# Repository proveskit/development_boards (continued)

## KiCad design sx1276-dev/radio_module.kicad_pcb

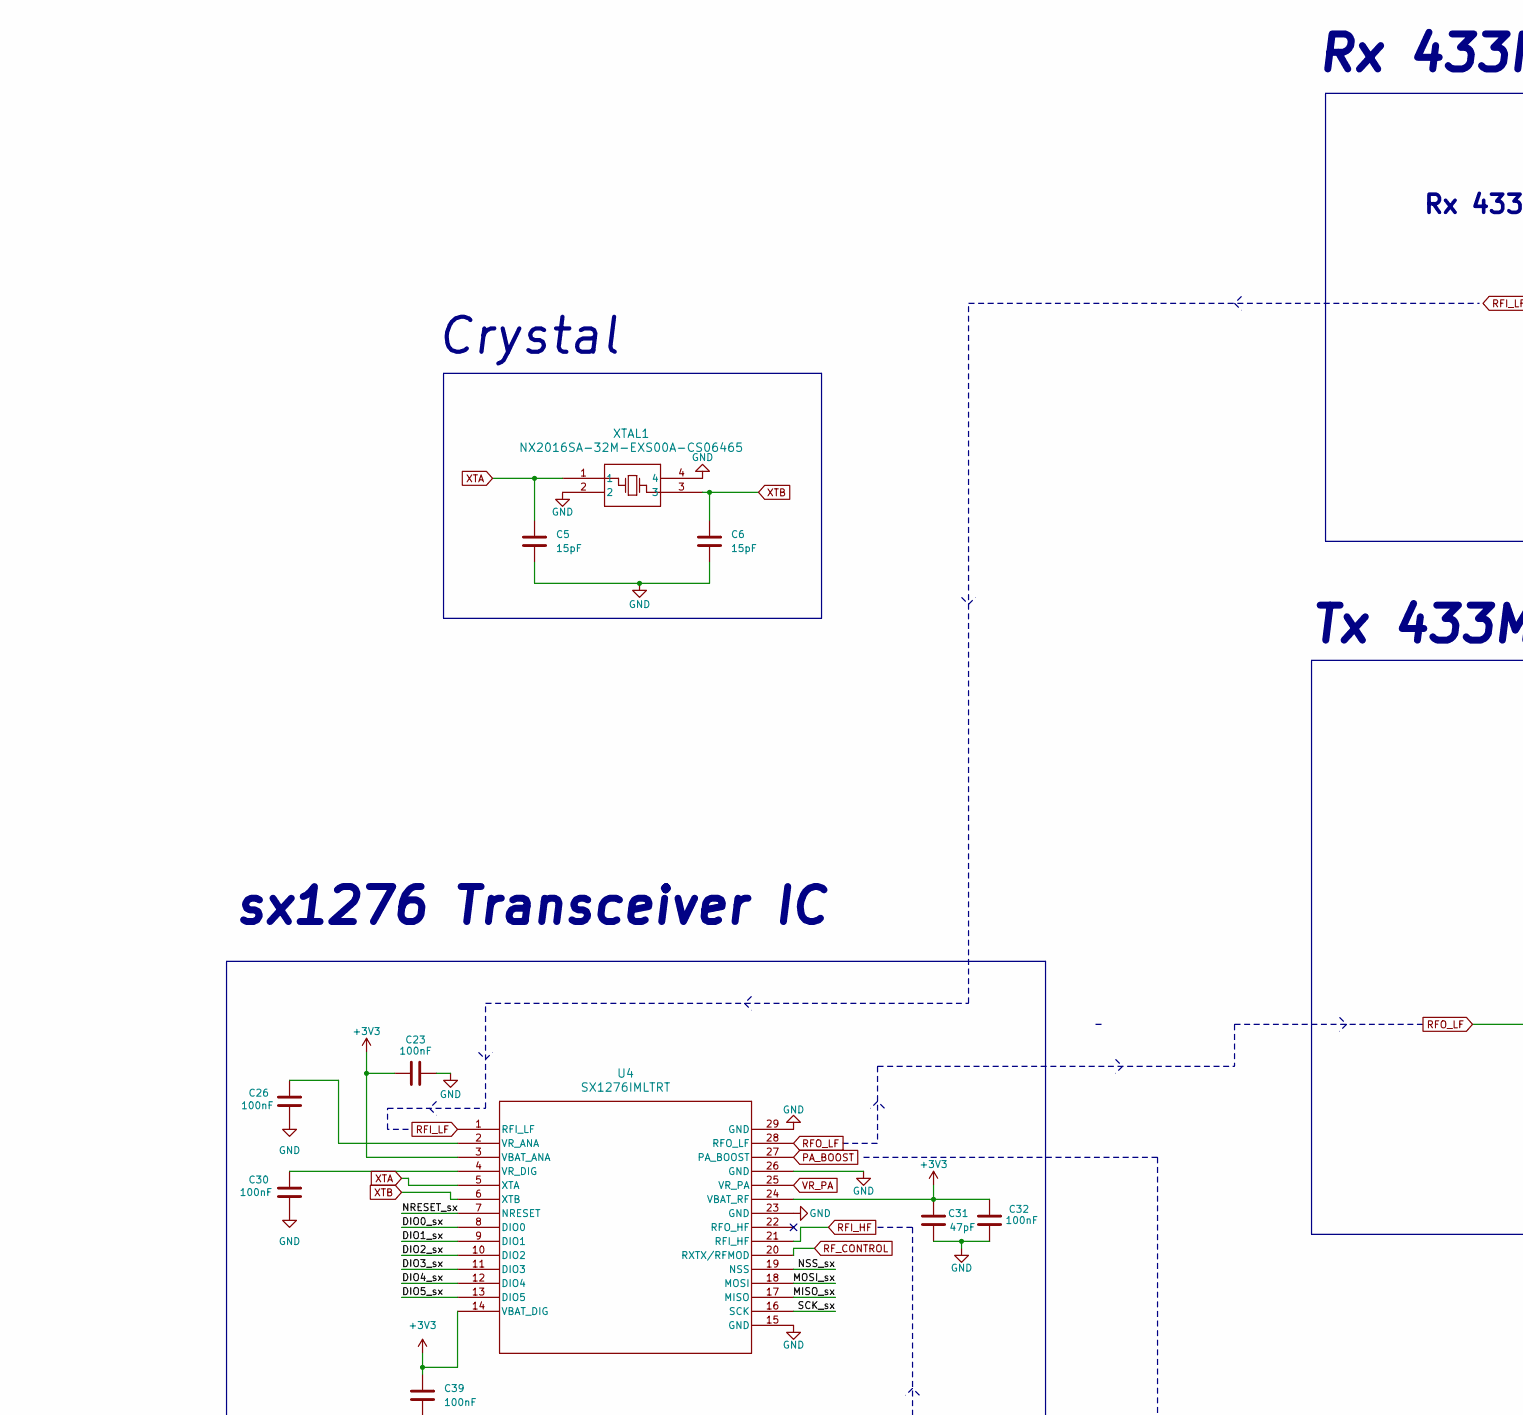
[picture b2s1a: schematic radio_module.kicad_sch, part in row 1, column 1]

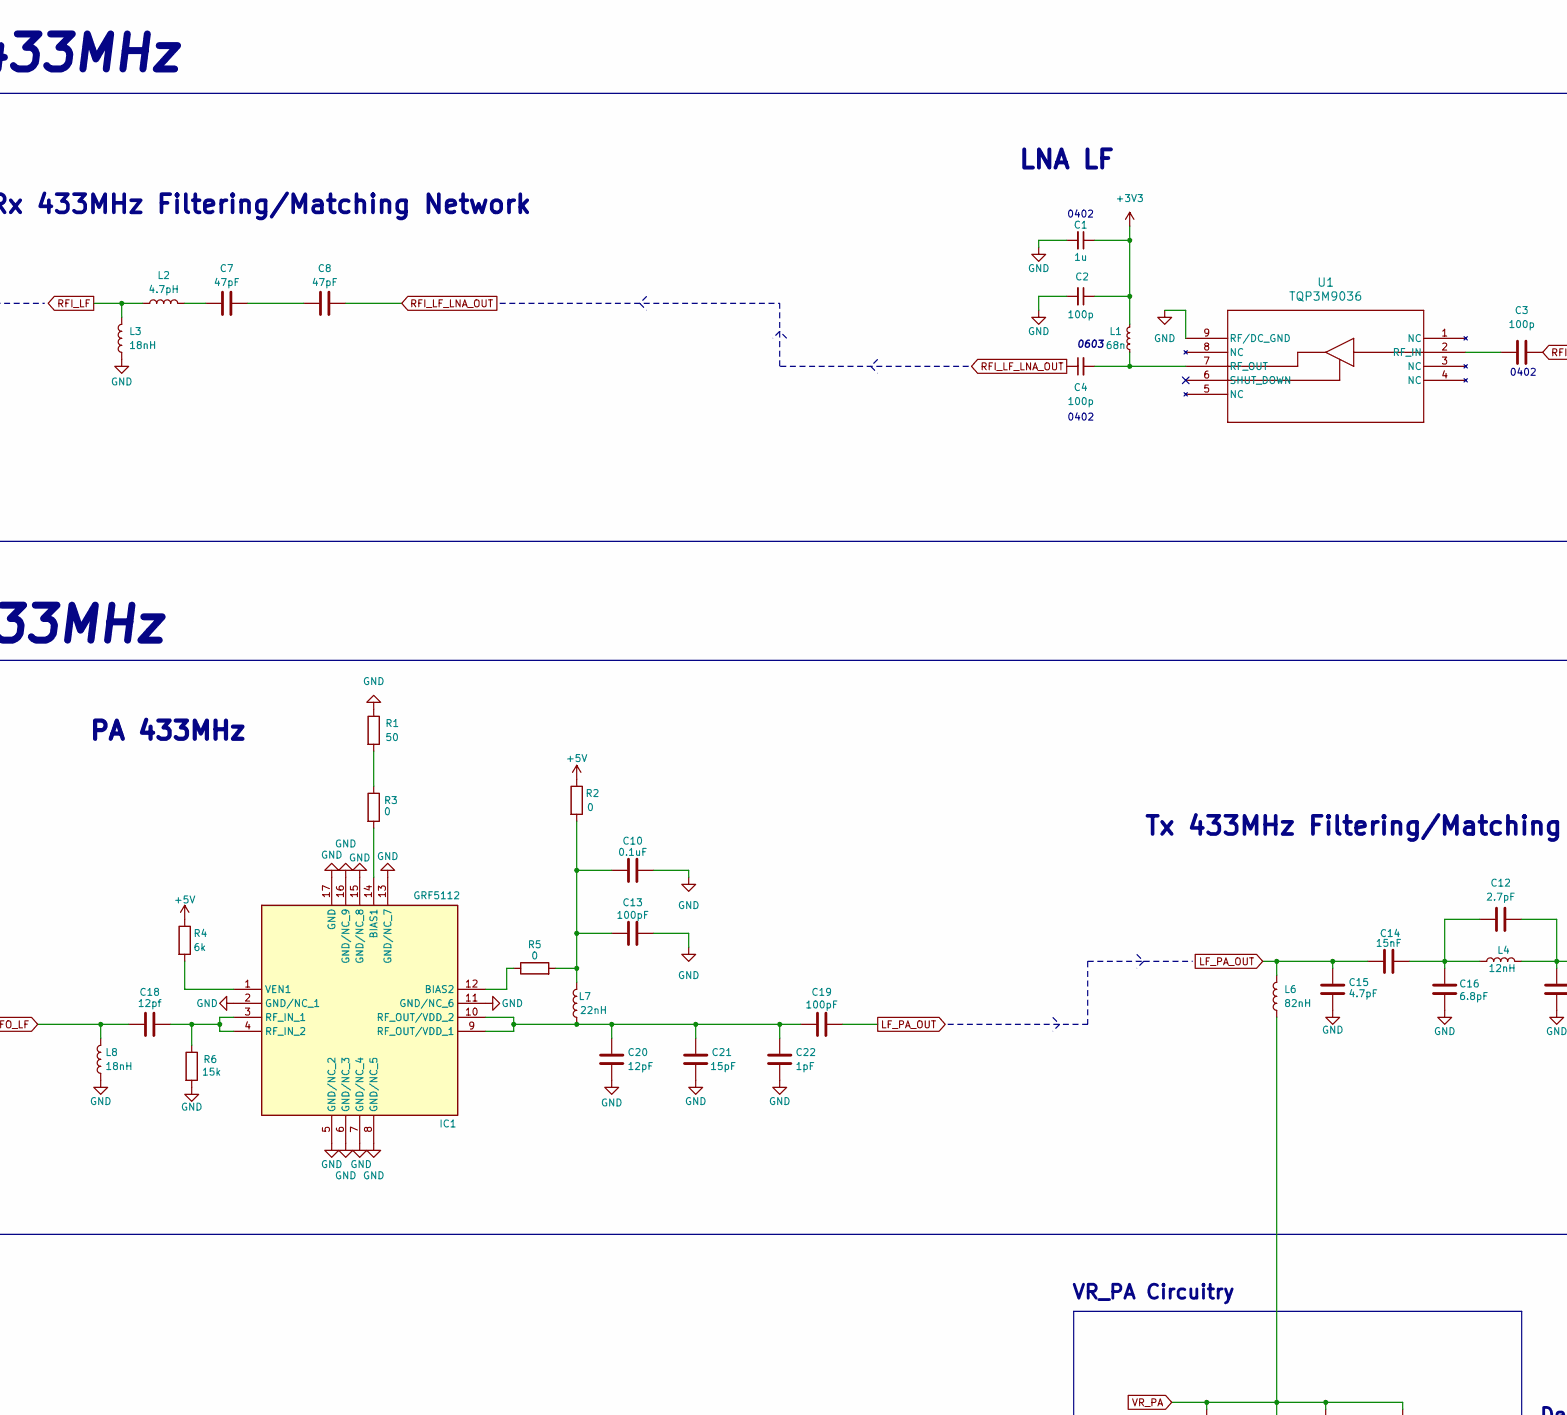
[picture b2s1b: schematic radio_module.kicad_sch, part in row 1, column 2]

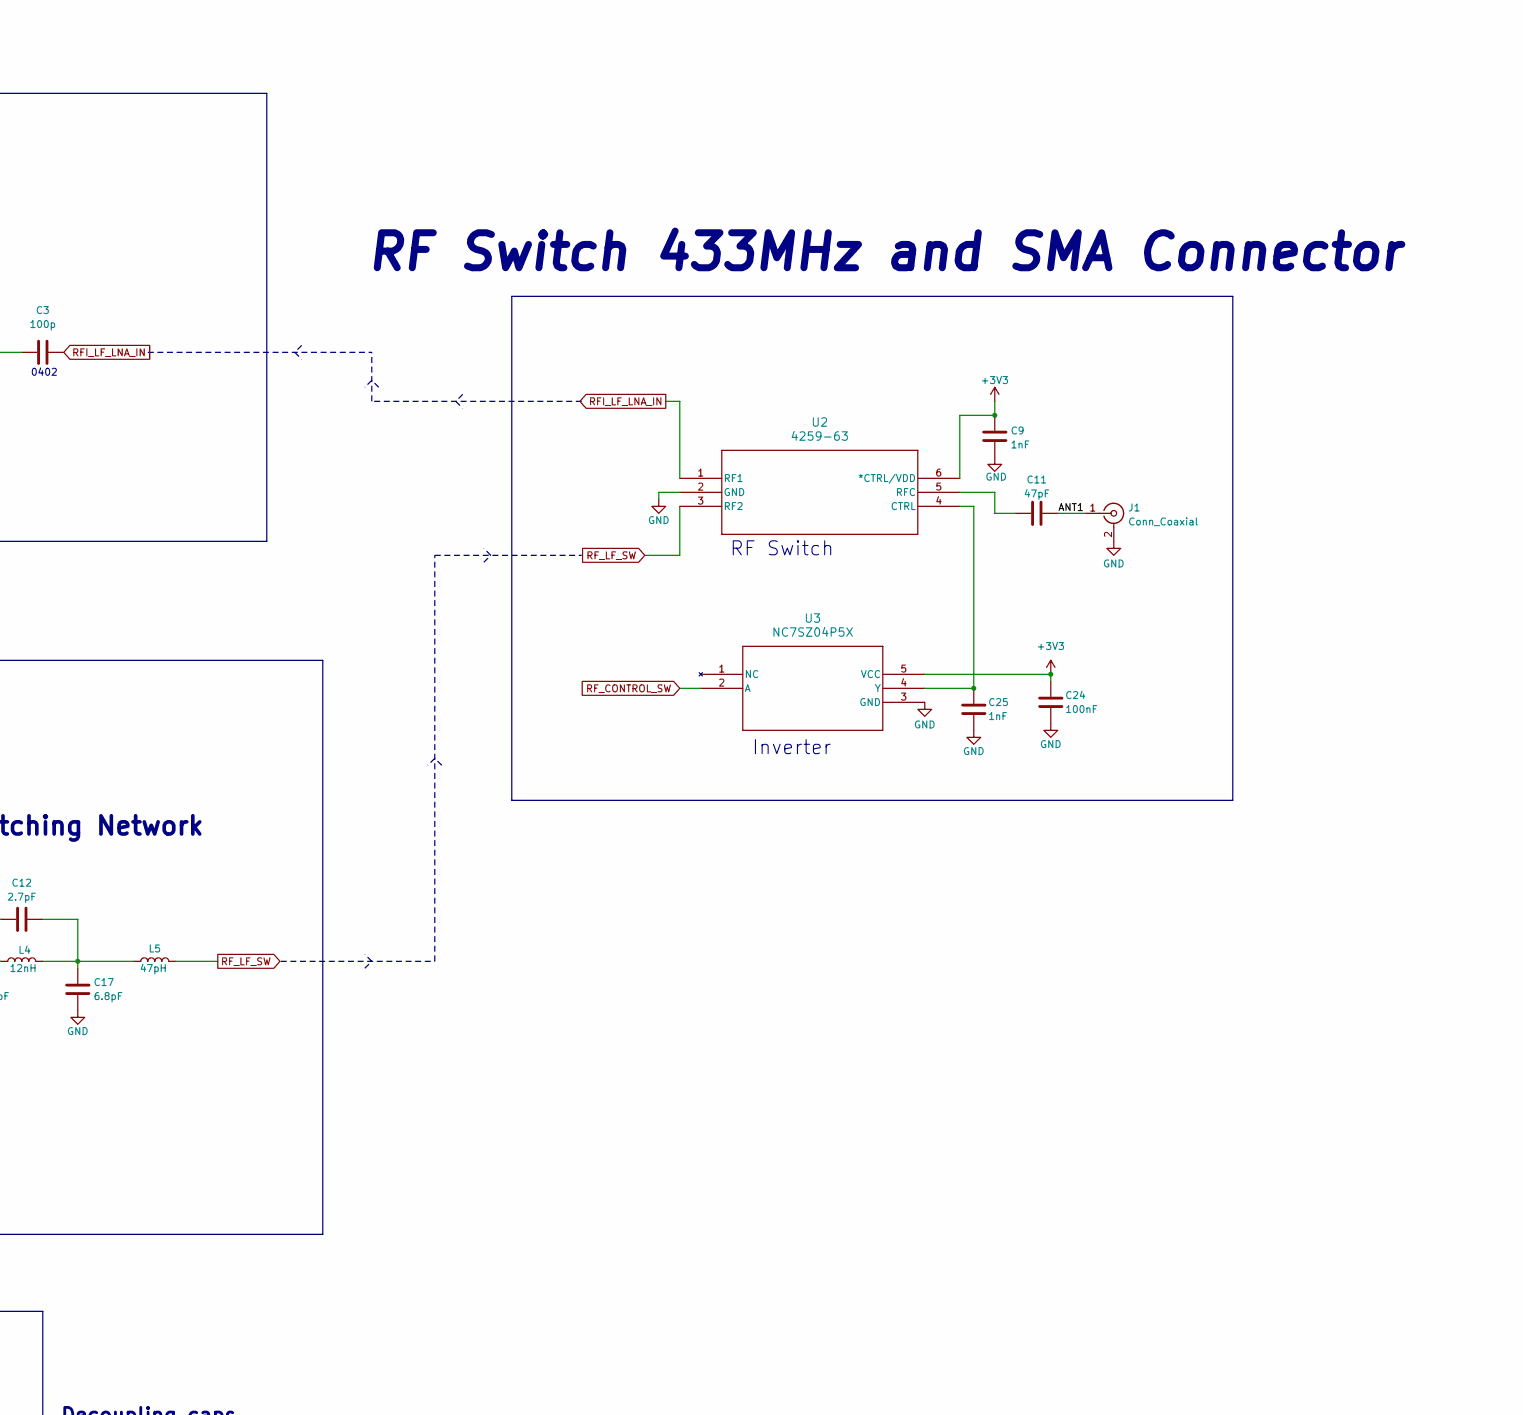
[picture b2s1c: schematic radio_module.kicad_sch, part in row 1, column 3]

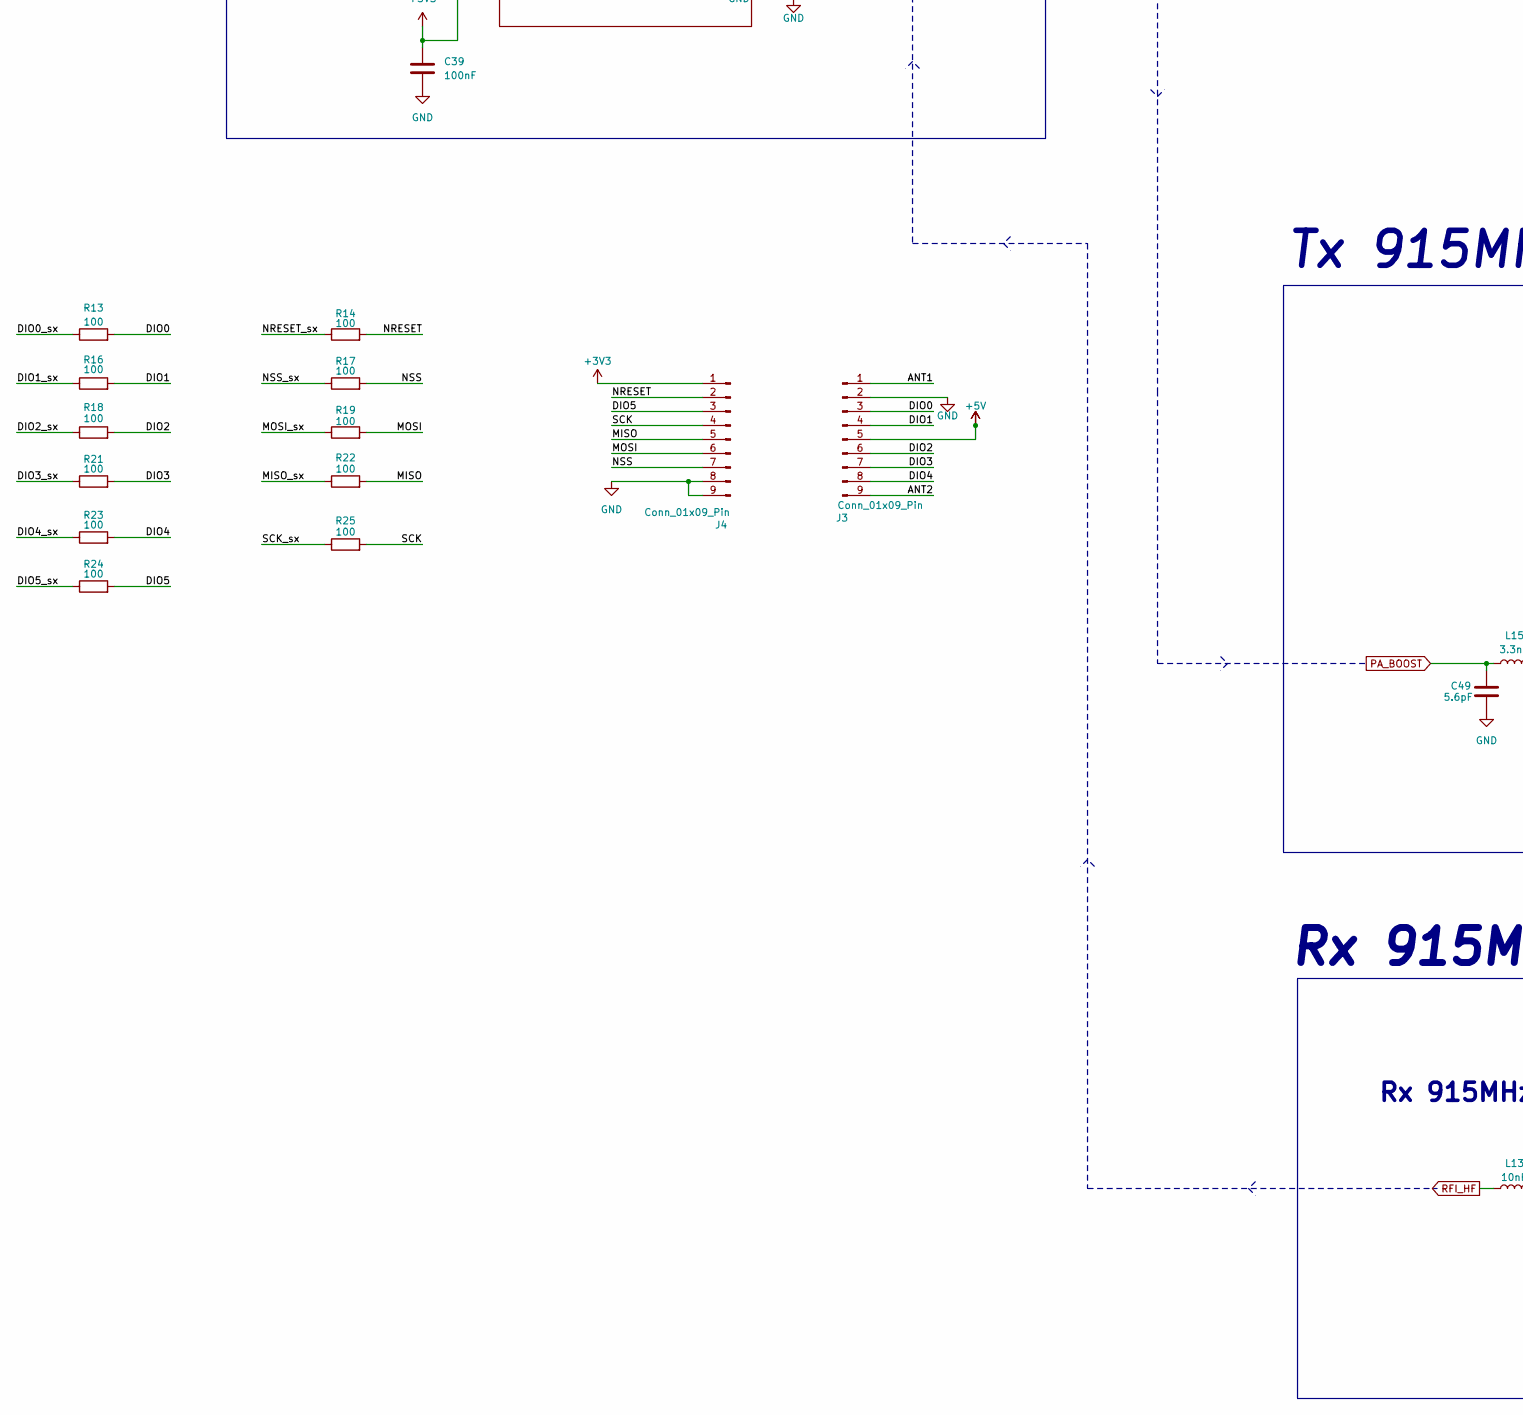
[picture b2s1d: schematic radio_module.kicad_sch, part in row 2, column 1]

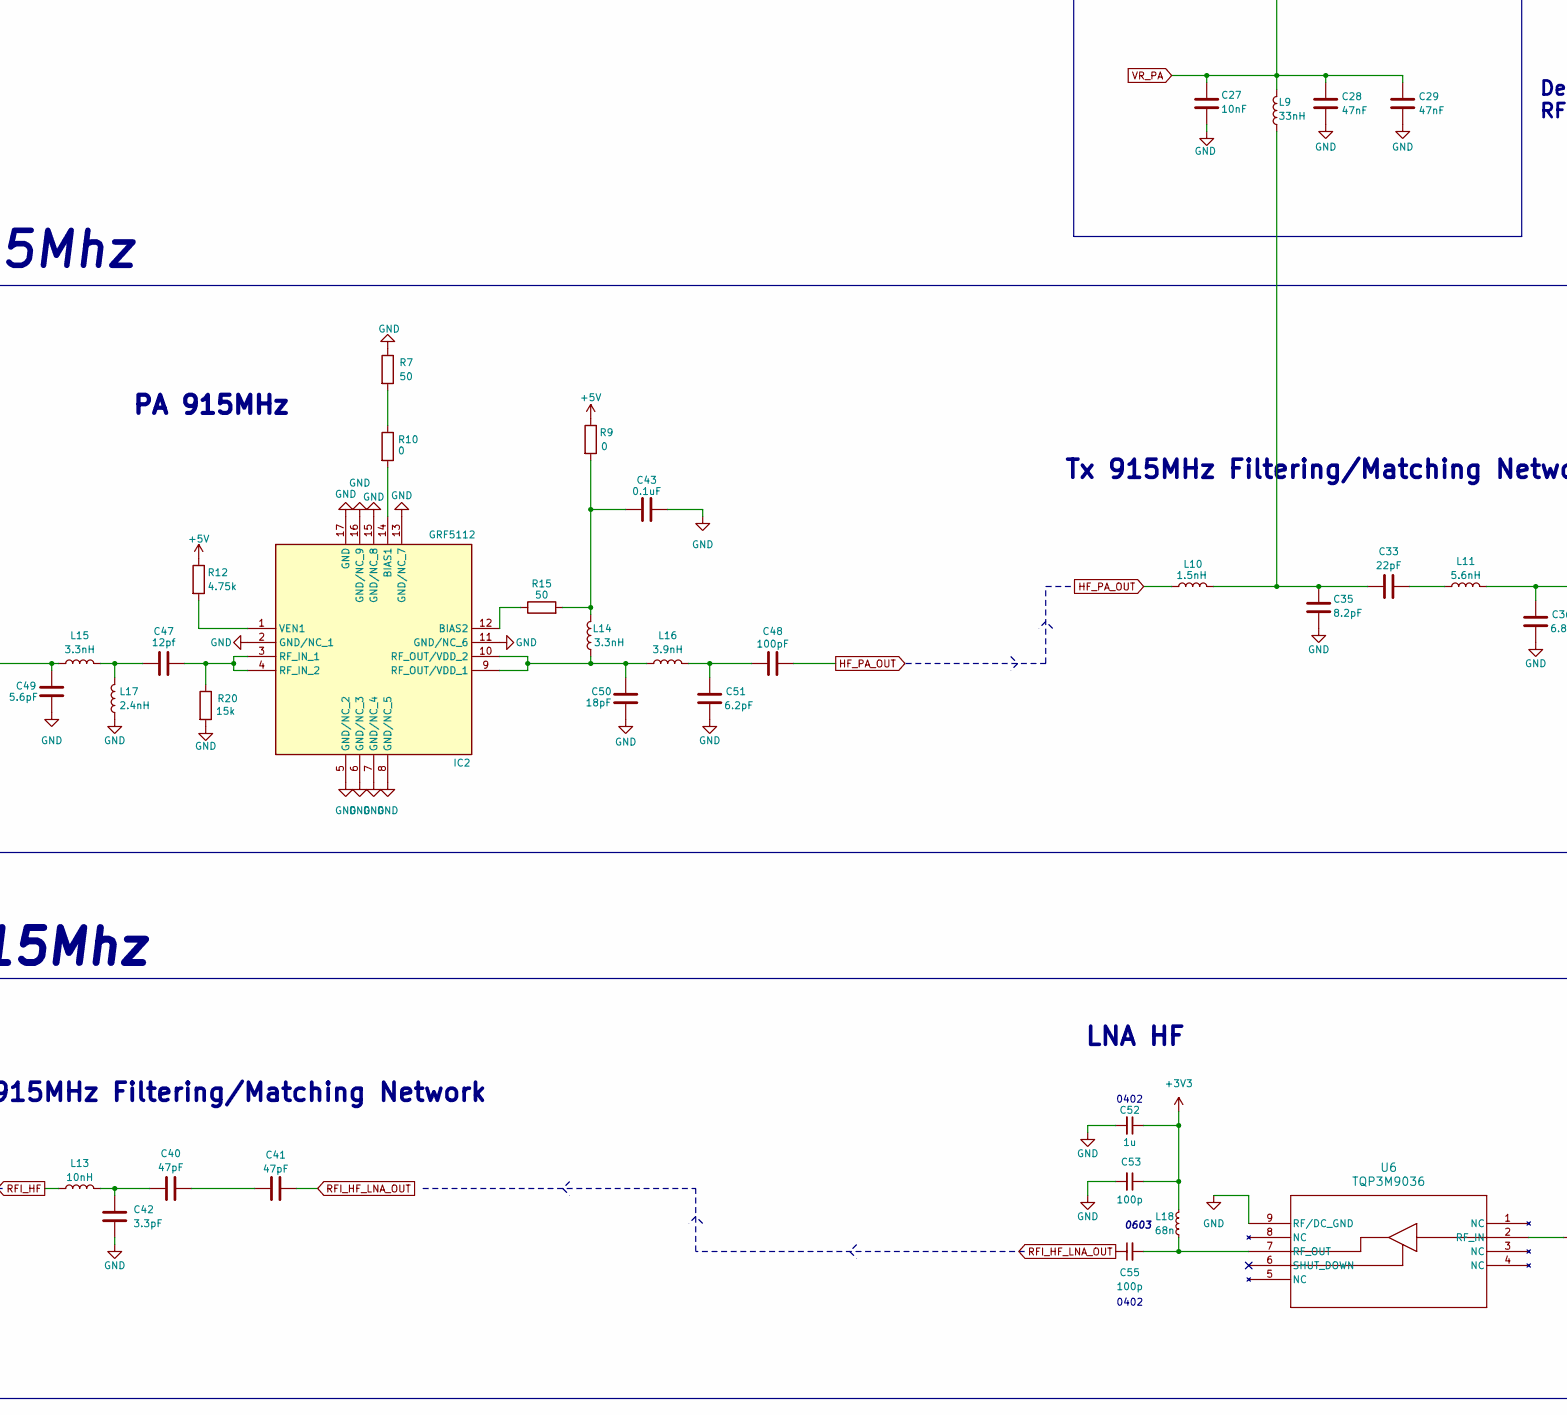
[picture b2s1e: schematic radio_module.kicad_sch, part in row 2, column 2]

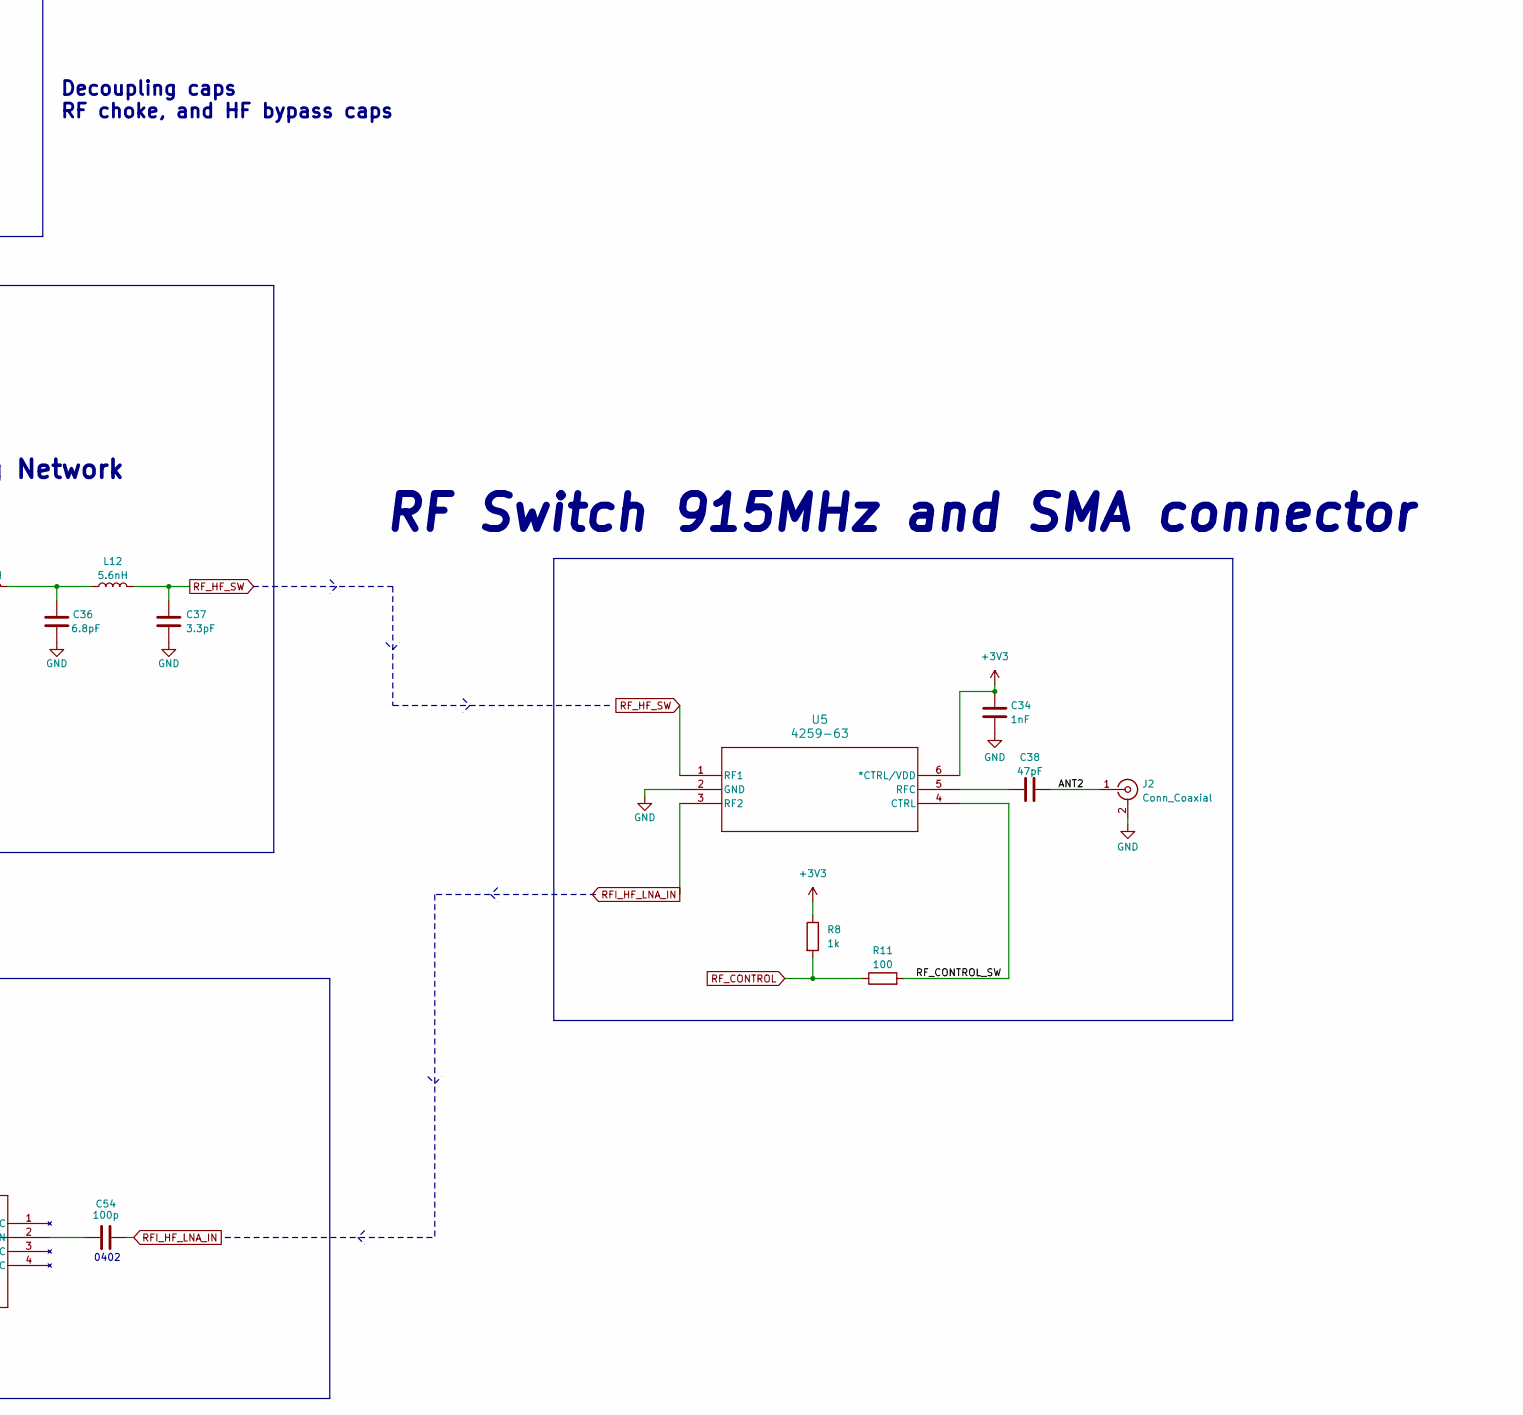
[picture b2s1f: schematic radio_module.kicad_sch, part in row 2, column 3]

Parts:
C1, C52: 1u; C_0402_1005Metric; MPN TMK107BJ105KAHT
C2, C4, C53, C55: 100p; C_0402_1005Metric; MPN C0402C101J5GACAUTO
C3, C54: 100p; C_0402_1005Metric
C5, C6, C21: 15pF; C_0402_1005Metric
C7, C8, C11, C31, C38, C40, C41: 47pF; C_0402_1005Metric
C9, C25, C34: 1nF; C_0402_1005Metric
C10, C43: 0.1uF; C_0402_1005Metric
C12: 2.7pF; C_0402_1005Metric
C13, C19, C48: 100pF; C_0402_1005Metric
C14: 15nF; C_0402_1005Metric
C15: 4.7pF; C_0402_1005Metric
C16, C17, C36: 6.8pF; C_0402_1005Metric
C18, C47: 12pf; C_0402_1005Metric
C20: 12pF; C_0402_1005Metric
C22: 1pF; C_0402_1005Metric
C23, C24, C26, C30, C32, C39: 100nF; C_0402_1005Metric
C27: 10nF; C_0402_1005Metric
C28, C29: 47nF; C_0402_1005Metric
C33: 22pF; C_0402_1005Metric
C35: 8.2pF; C_0402_1005Metric
C37, C42: 3.3pF; C_0402_1005Metric
C49: 5.6pF; C_0402_1005Metric
C50: 18pF; C_0402_1005Metric
C51: 6.2pF; C_0402_1005Metric
IC1, IC2: GRF5112; QFN50P300X300X90-17N; Manufacturer_Part_Number GRF5112
J1, J2: Conn_Coaxial; SMA_Amphenol_901-144_Vertical
J3, J4: Conn_01x09_Pin; PinSocket_1x09_P1.00mm_Vertical
L1, L18: 68n; L_0603_1608Metric; MPN LQW18AN68NG8ZD
L2: 4.7pH; L_0402_1005Metric
L3, L8: 18nH; L_0402_1005Metric
L4: 12nH; L_0402_1005Metric
L5: 47pH; L_0402_1005Metric
L6: 82nH; L_0402_1005Metric
L7: 22nH; L_0402_1005Metric
L9: 33nH; L_0402_1005Metric
L10: 1.5nH; L_0402_1005Metric
L11, L12: 5.6nH; L_0402_1005Metric
L13: 10nH; L_0402_1005Metric
L14, L15: 3.3nH; L_0402_1005Metric
L16: 3.9nH; L_0402_1005Metric
L17: 2.4nH; L_0402_1005Metric
R1, R7, R15: 50; R_0402_1005Metric
R2, R3, R5, R9, R10: 0; R_0402_1005Metric
R4: 6k; R_0402_1005Metric
R6, R20: 15k; R_0402_1005Metric
R8: 1k; R_0402_1005Metric
R11, R13, R14, R16, R17, R18, R19, R21, R22, R23, R24, R25: 100; R_0402_1005Metric
R12: 4.75k; R_0402_1005Metric
U1, U6: TQP3M9036; DFN8_2x2_QOR
U2, U5: 4259-63; SC-70-6_PSM
U3: NC7SZ04P5X; SC-88A-5_1P35X2P2_ONS
U4: SX1276IMLTRT; QFN28_6X6_SEM
XTAL1: NX2016SA-32M-EXS00A-CS06465; NX2016SA_NDK

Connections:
+3V3: C1.1, C2.1, C9.1, C23.1, C24.1, C31.1, C32.2, C34.1, C39.1, C52.1, C53.1, J4.1, L1.1, L18.1, R8.1, U2.6 (*CTRL/VDD), U3.5 (VCC), U4.3 (VBAT_ANA), U4.14 (VBAT_DIG), U4.24 (VBAT_RF), U5.6 (*CTRL/VDD)
+5V: J3.5, R2.1, R4.1, R9.1, R12.1
/ANT1: C11.2, J1.1 (In), J3.1
/ANT2: C38.1, J2.1 (In), J3.9
/DIO0: J3.3, R13.2
/DIO0_sx: R13.1, U4.8 (DIO0)
/DIO1: J3.4, R16.2
/DIO1_sx: R16.1, U4.9 (DIO1)
/DIO2: J3.6, R18.2
/DIO2_sx: R18.1, U4.10 (DIO2)
/DIO3: J3.7, R21.2
/DIO3_sx: R21.1, U4.11 (DIO3)
/DIO4: J3.8, R23.2
/DIO4_sx: R23.1, U4.12 (DIO4)
/DIO5: J4.3, R24.2
/DIO5_sx: R24.1, U4.13 (DIO5)
/MISO: J4.5, R22.2
/MISO_sx: R22.1, U4.17 (MISO)
/MOSI: J4.6, R19.2
/MOSI_sx: R19.1, U4.18 (MOSI)
/NRESET: J4.2, R14.2
/NRESET_sx: R14.1, U4.7 (NRESET)
/NSS: J4.7, R17.2
/NSS_sx: R17.1, U4.19 (NSS)
/SCK: J4.4, R25.2
/SCK_sx: R25.1, U4.16 (SCK)
GND: C1.2, C2.2, C5.2, C6.2, C9.2, C10.2, C13.2, C15.2, C16.1, C17.1, C20.2, C21.2, C22.2, C23.2, C24.2, C25.2, C26.1, C27.2, C28.2, C29.2, C30.1, C31.2, C32.1, C34.2, C35.2, C36.1, C37.2, C39.2, C42.2, C43.2, C49.2, C50.2, C51.2, C52.2, C53.2, IC1.2 (GND/NC_1), IC1.5 (GND/NC_2), IC1.6 (GND/NC_3), IC1.7 (GND/NC_4), IC1.8 (GND/NC_5), IC1.11 (GND/NC_6), IC1.13 (GND/NC_7), IC1.15 (GND/NC_8), IC1.16 (GND/NC_9), IC1.17 (GND), IC2.2 (GND/NC_1), IC2.5 (GND/NC_2), IC2.6 (GND/NC_3), IC2.7 (GND/NC_4), IC2.8 (GND/NC_5), IC2.11 (GND/NC_6), IC2.13 (GND/NC_7), IC2.15 (GND/NC_8), IC2.16 (GND/NC_9), IC2.17 (GND), J1.2 (Ext), J2.2 (Ext), J3.2, J4.8, J4.9, L3.1, L8.1, L17.1, R1.1, R6.2, R7.1, R20.2, U1.9 (RF/DC_GND), U2.2 (GND), U3.3 (GND), U4.15 (GND), U4.23 (GND), U4.26 (GND), U4.29 (GND), U5.2 (GND), U6.9 (RF/DC_GND), XTAL1.2, XTAL1.4
HF_PA_OUT: C48.2, L10.1
LF_PA_OUT: C14.1, C15.1, C19.2, L6.2
unnamed: C7.1, L2.2
unnamed: C7.2, C8.1
unnamed: C10.1, C13.1, L7.2, R2.2, R5.2
unnamed: C12.1, C14.2, C16.2, L4.1
unnamed: C12.2, C17.2, L4.2, L5.1
unnamed: C33.1, C35.1, L9.1, L10.2
unnamed: C33.2, L11.1
unnamed: C36.2, L11.2, L12.1
unnamed: C40.1, C42.1, L13.2
unnamed: C40.2, C41.1
unnamed: C43.1, L14.2, R9.2, R15.2
unnamed: C47.1, L15.2, L17.2
unnamed: C48.1, C51.1, L16.2
unnamed: IC1.14 (BIAS1), R3.2
unnamed: IC1.12 (BIAS2), R5.1
unnamed: C18.2, IC1.3 (RF_IN_1), IC1.4 (RF_IN_2), R6.1
unnamed: C19.1, C20.1, C21.1, C22.1, IC1.9 (RF_OUT/VDD_1), IC1.10 (RF_OUT/VDD_2), L7.1
unnamed: IC1.1 (VEN1), R4.2
unnamed: IC2.14 (BIAS1), R10.2
unnamed: IC2.12 (BIAS2), R15.1
unnamed: C47.2, IC2.3 (RF_IN_1), IC2.4 (RF_IN_2), R20.1
unnamed: C50.1, IC2.9 (RF_OUT/VDD_1), IC2.10 (RF_OUT/VDD_2), L14.1, L16.1
unnamed: IC2.1 (VEN1), R12.2
unnamed: R1.2, R3.1
unnamed: R7.2, R10.1
unnamed: C3.2, U1.2 (RF_IN)
unnamed: C4.2, L1.2, U1.7 (RF_OUT)
unnamed: C25.1, U2.4 (CTRL), U3.4 (Y)
unnamed: C11.1, U2.5 (RFC)
unnamed: C26.2, U4.2 (VR_ANA)
unnamed: C30.2, U4.4 (VR_DIG)
unnamed: C38.2, U5.5 (RFC)
unnamed: C54.2, U6.2 (RF_IN)
unnamed: C55.2, L18.2, U6.7 (RF_OUT)
PA_BOOST: C49.1, L15.1, U4.27 (PA_BOOST)
RFI_HF: L13.1, U4.21 (RFI_HF)
RFI_HF_LNA_IN: C54.1, U5.3 (RF2)
RFI_HF_LNA_OUT: C41.2, C55.1
RFI_LF: L2.1, L3.2, U4.1 (RFI_LF)
RFI_LF_LNA_IN: C3.1, U2.1 (RF1)
RFI_LF_LNA_OUT: C4.1, C8.2
RFO_LF: C18.1, L8.2, U4.28 (RFO_LF)
RF_CONTROL: R8.2, R11.1, U4.20 (RXTX/RFMOD)
RF_CONTROL_SW: R11.2, U3.2 (A), U5.4 (CTRL)
RF_HF_SW: C37.1, L12.2, U5.1 (RF1)
RF_LF_SW: L5.2, U2.3 (RF2)
VR_PA: C27.1, C28.1, C29.1, L6.1, L9.2, U4.25 (VR_PA)
XTA: C5.1, U4.5 (XTA), XTAL1.1
XTB: C6.1, U4.6 (XTB), XTAL1.3

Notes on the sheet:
Inverter
PA 915MHz
Tx 915MHz Filtering/Matching Network
Crystal
RF Switch 433MHz and SMA Connector
0402
0603
Tx 915Mhz
RF Switch
PA 433MHz
Tx 433MHz Filtering/Matching Network
VR_PA Circuitry
Rx 915Mhz
Decoupling caps RF choke, and HF bypass caps
LNA LF
RF Switch 915MHz and SMA connector
Rx 433MHz
LNA HF
sx1276 Transceiver IC
Tx 433MHz
Rx 433MHz Filtering/Matching Network
Rx 915MHz Filtering/Matching Network

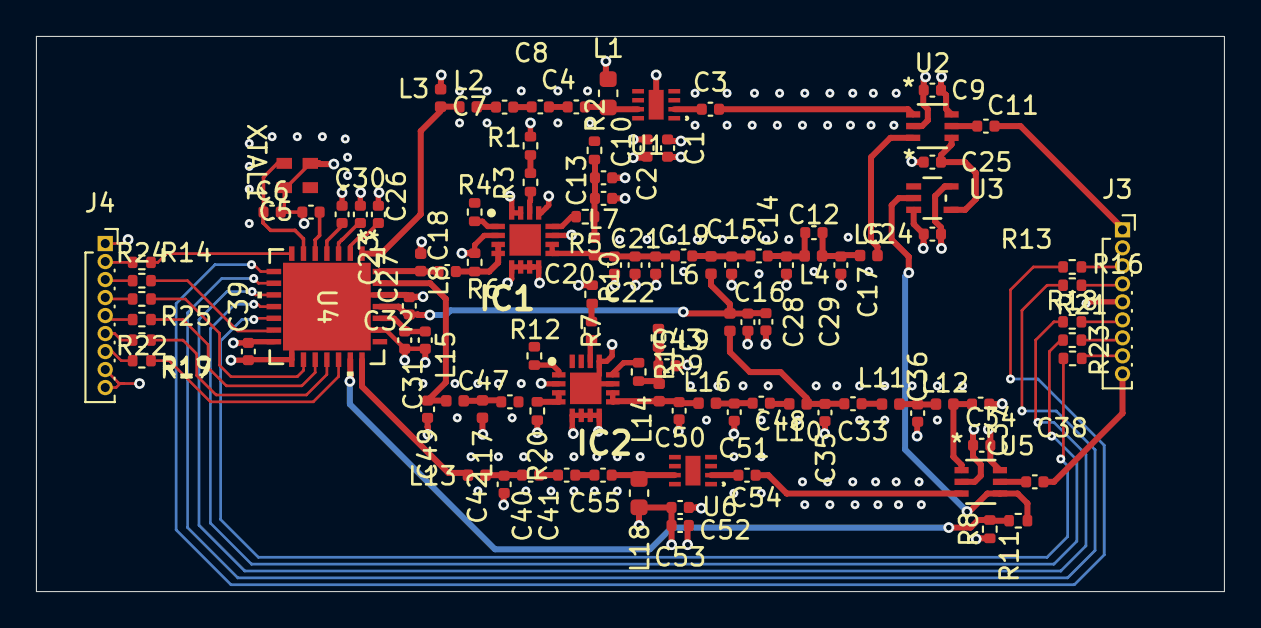
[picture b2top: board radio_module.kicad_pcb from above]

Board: 4 copper layers, 66.0 x 30.8 mm, 106 parts (0 on the bottom side), 78 nets.

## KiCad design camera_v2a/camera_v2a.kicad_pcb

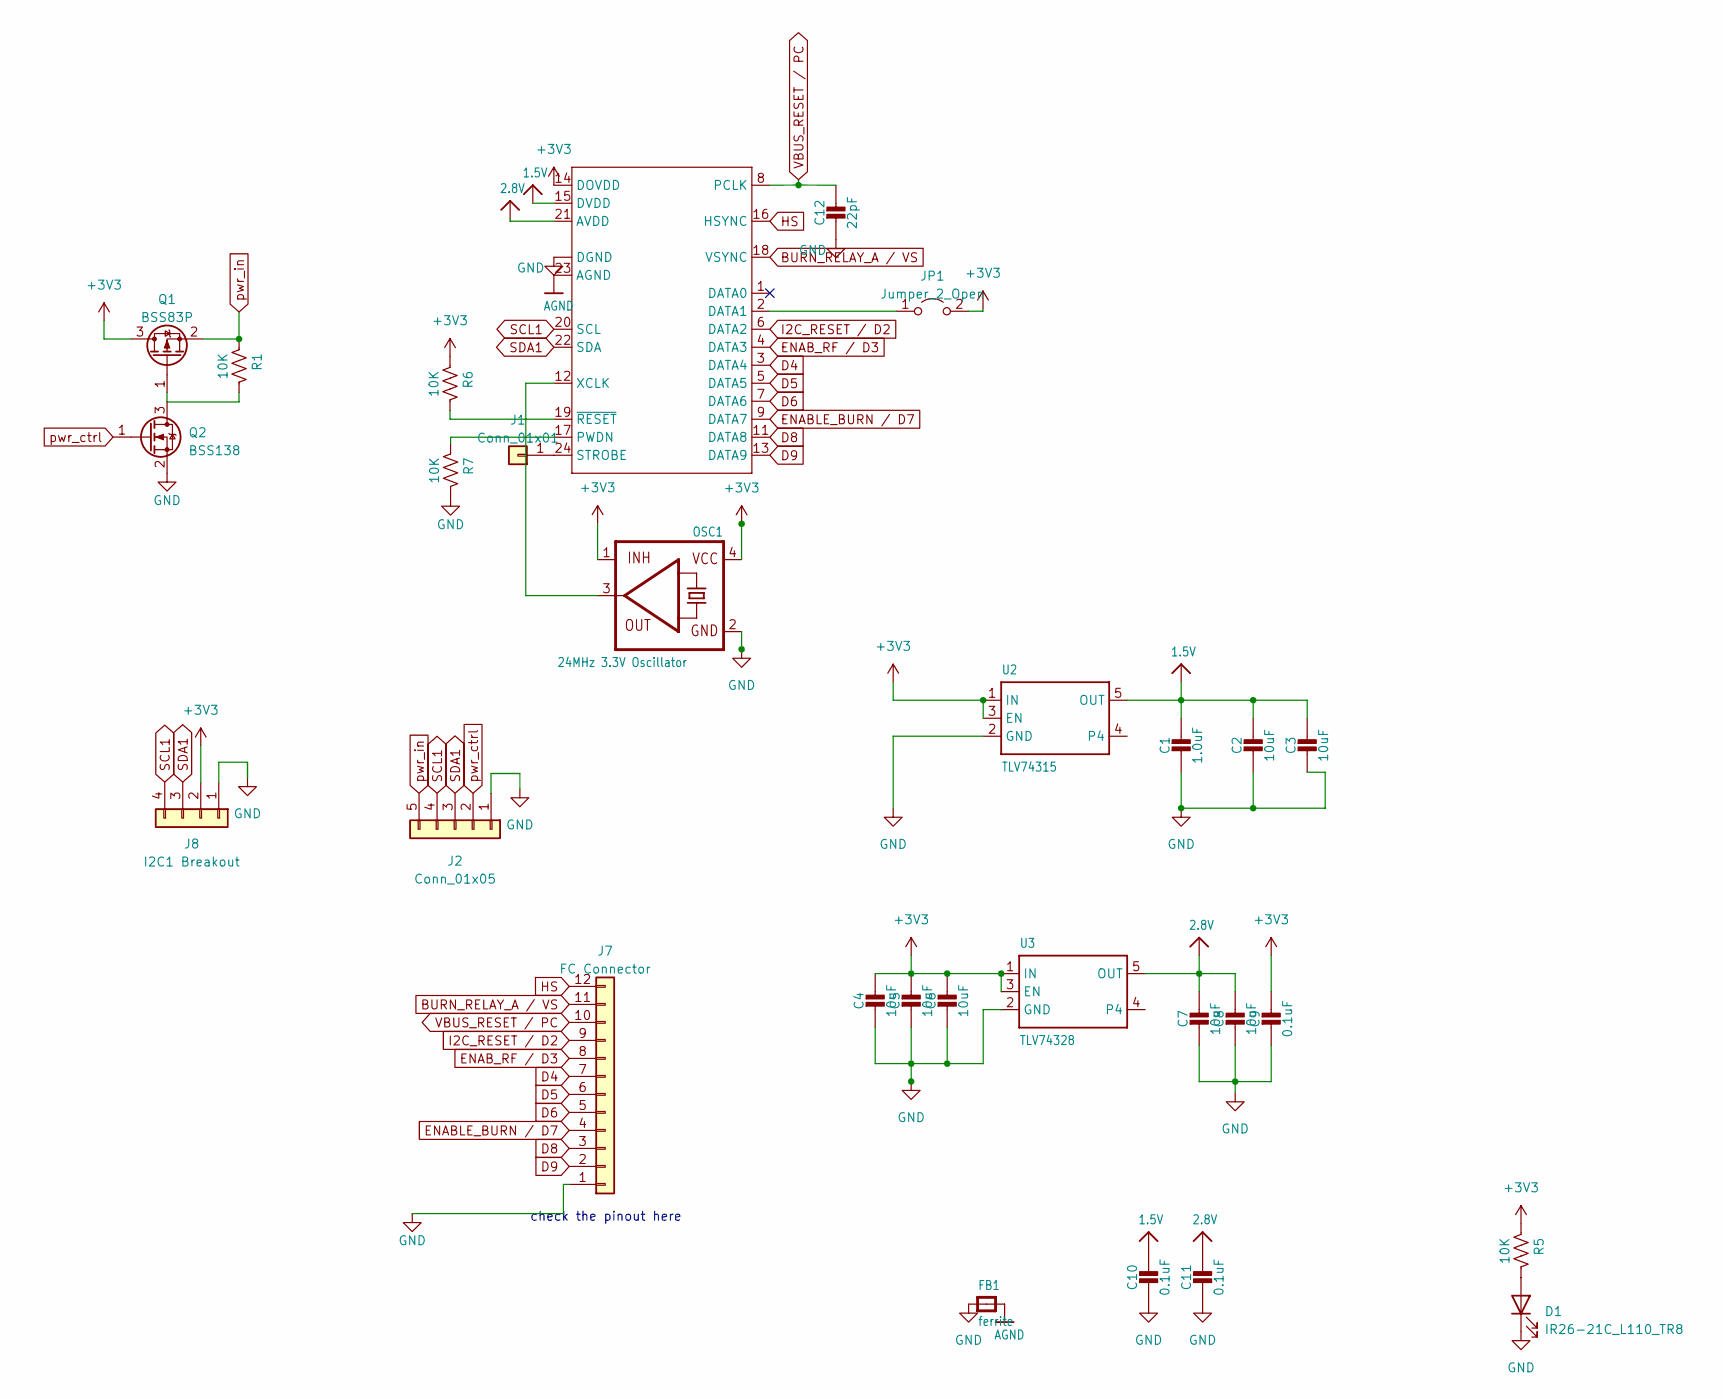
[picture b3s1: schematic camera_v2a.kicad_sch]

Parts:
C1: 1.0uF; C_0603_1608Metric_Pad1.08x0.95mm_HandSolder
C2, C3, C4, C5, C6, C7, C8: 10uF; C_0805_2012Metric_Pad1.18x1.45mm_HandSolder
C9, C10, C11: 0.1uF; C_0603_1608Metric_Pad1.08x0.95mm_HandSolder
C12: 22pF; C_0603_1608Metric_Pad1.08x0.95mm_HandSolder
D1: IR26-21C_L110_TR8; LED_0603_1608Metric_Pad1.05x0.95mm_HandSolder
FB1: ferrite; R_0603_1608Metric_Pad0.98x0.95mm_HandSolder
J1: Conn_01x01; TestPoint_Pad_D1.5mm
J2: Conn_01x05; PinHeader_1x05_P2.54mm_Vertical
J7: FC Connector; Molex_Pico-Lock_504050-1291_1x12-1MP_P1.50mm_Horizontal
J8: I2C1 Breakout; JST_SH_BM04B-SRSS-TB_1x04-1MP_P1.00mm_Vertical
JP1: Jumper_2_Open; SolderJumper-2_P1.3mm_Open_RoundedPad1.0x1.5mm
OSC1: 24MHz 3.3V Oscillator; Oscillator_SMD_SeikoEpson_SG8002CE-4Pin_3.2x2.5mm_HandSolde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
Q1: BSS83P; SOT-23
Q2: BSS138; SOT-23
R1, R5, R6, R7: 10K; R_0603_1608Metric
U2: TLV74315; SOT-23-5_HandSoldering; JLC_ROTATION 0
U3: TLV74328; SOT-23-5_HandSoldering; JLC_ROTATION 0
X1: CAMERA_OV2640; Molex_502244-2430_1x24-1MP_P0.5mm_Horizontal

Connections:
1.5V: C1.1, C2.1, C3.1, C10.1, U2.5 (OUT), X1.15 (DVDD)
2.8V: C7.1, C8.1, C11.1, U3.5 (OUT), X1.21 (AVDD)
+3V3: C4.1, C5.1, C6.1, C9.1, J8.2, JP1.2 (B), OSC1.1 (INH), OSC1.4 (VCC), Q1.3 (D), R5.1, R6.1, U2.1 (IN), U2.3 (EN), U3.1 (IN), U3.3 (EN), X1.14 (DOVDD)
AGND: FB1.2, X1.23 (AGND)
BURN_RELAY_A / VS: J7.11, X1.18 (VSYNC)
D4: J7.7, X1.3 (DATA4)
D5: J7.6, X1.5 (DATA5)
D6: J7.5, X1.7 (DATA6)
D8: J7.3, X1.11 (DATA8)
D9: J7.2, X1.13 (DATA9)
ENABLE_BURN / D7: J7.4, X1.9 (DATA7)
ENAB_RF / D3: J7.8, X1.4 (DATA3)
GND: C1.2, C2.2, C3.2, C4.2, C5.2, C6.2, C7.2, C8.2, C9.2, C10.2, C11.2, C12.2, D1.1 (K), FB1.1, J2.1, J7.1, J8.1, OSC1.2 (GND), Q2.2 (S), R7.2, U2.2 (GND), U3.2 (GND), X1.10 (DGND), X1.SPRT1 (DGND), X1.SPRT2 (DGND)
HS: J7.12, X1.16 (HSYNC)
I2C_RESET / D2: J7.9, X1.6 (DATA2)
unnamed: D1.2 (A), R5.2
unnamed: J1.1, X1.24 (STROBE)
unnamed: JP1.1 (A), X1.2 (DATA1)
unnamed: OSC1.3 (OUT), X1.12 (XCLK)
unnamed: Q1.1 (G), Q2.3 (D)
unnamed: R7.1, X1.17 (PWDN)
unnamed: R6.2, X1.19 (~RESET)
SCL1: J2.4, J8.4, X1.20 (SCL)
SDA1: J2.3, J8.3, X1.22 (SDA)
VBUS_RESET / PC: C12.1, J7.10, X1.8 (PCLK)
pwr_ctrl: J2.2, Q2.1 (G)
pwr_in: J2.5, Q1.2 (S), R1.1

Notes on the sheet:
check the pinout here

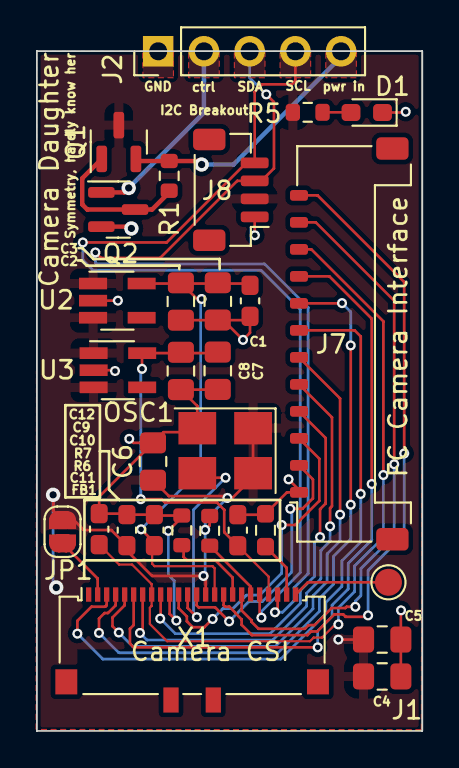
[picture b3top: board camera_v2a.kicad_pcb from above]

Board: 2 copper layers, 21.4 x 37.8 mm, 29 parts (0 on the bottom side), 27 nets.
